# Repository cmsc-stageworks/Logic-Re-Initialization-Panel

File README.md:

# Logic Initialization Panel

Created by the BYU IEEE Branch for the CMSC

## Overview
The idea is that you take an isolinear chip that is "broken" and you place it in to have a certain logic circuit "fixed/repaired" the screen gives you a guide to be able to solve the puzzle/prompt. you then "write" it to the card

### Puzzle setup
The puzzle would consist of a series of (up to) 4 inputs and (up to) 4 outputs. These inputs could be things such as "Engine overheating" or "Autorization level 4 is given" or "Fire detected". The outputs could be "Turn on cooling fans" or "Override safety protocols" or "open airlock" etc. The user would be responsible for implemmenting the logic necessary to solve the puzzle at hand. 

### Interactivity
The user can test inputs manually by pressing the 4 buttons off to the input side of the logic panel, turning them on or off (true or false). They can then visually see how the logic would travel step by step in their current circuit.

### Completion
When they are ready to submit they hit the write button and it tests their circuit to verify correctness. If it is incorrect it throws an error and lets them try again. If it is correct it "writes" it to the card and they can move the card back to its original position to "fix" or "optimize" a system

## Learning outcomes
This panel teaches basic boolean logic (not, and, or) to children, or can be configured to challenge adults with more gates/configurations.

### Gate holder

### Initial Concept
Will be cut down, since this was originally started as a whole panel idea and was cut down to be a sub-panel.

### Magnet Codes:
[logic_puzzle_addresses.txt](logic_puzzle_addresses.txt)
### File system
[Proposed File System](FileSystem.md)

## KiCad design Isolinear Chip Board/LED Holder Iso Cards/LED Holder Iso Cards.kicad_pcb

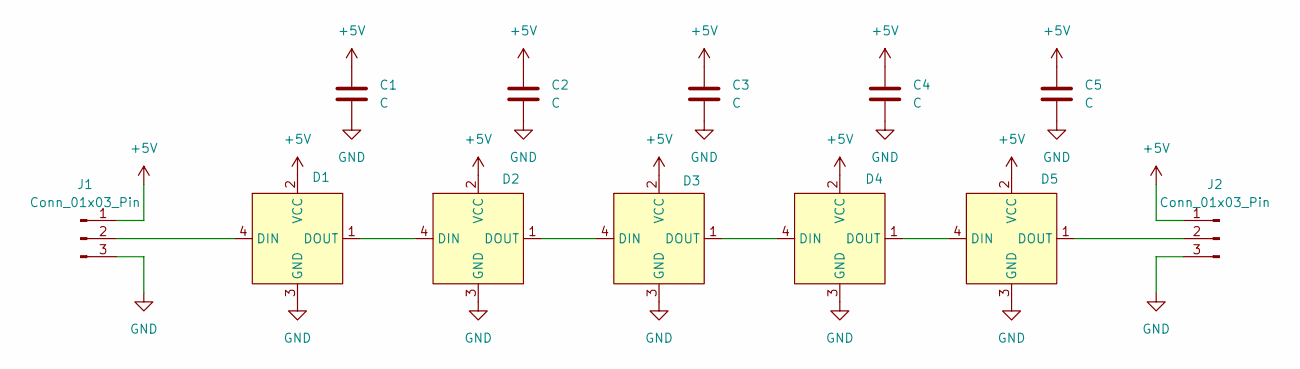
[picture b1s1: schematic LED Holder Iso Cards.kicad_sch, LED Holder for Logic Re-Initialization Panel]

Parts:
C1, C2, C3, C4, C5: C; C_Disc_D3.0mm_W1.6mm_P2.50mm
D1, D2, D3, D4, D5: NeoPixel_THT; LED_D5.0mm-4_RGB_Staggered_Pins
J1, J2: Conn_01x03_Pin; JST_XH_B3B-XH-AM_1x03_P2.50mm_Vertical

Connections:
+5V: C1.1, C2.1, C3.1, C4.1, C5.1, D1.2 (VCC), D2.2 (VCC), D3.2 (VCC), D4.2 (VCC), D5.2 (VCC), J1.1, J2.1
GND: C1.2, C2.2, C3.2, C4.2, C5.2, D1.3 (GND), D2.3 (GND), D3.3 (GND), D4.3 (GND), D5.3 (GND), J1.3, J2.3
unnamed: D1.4 (DIN), J1.2
unnamed: D1.1 (DOUT), D2.4 (DIN)
unnamed: D2.1 (DOUT), D3.4 (DIN)
unnamed: D3.1 (DOUT), D4.4 (DIN)
unnamed: D4.1 (DOUT), D5.4 (DIN)
unnamed: D5.1 (DOUT), J2.2

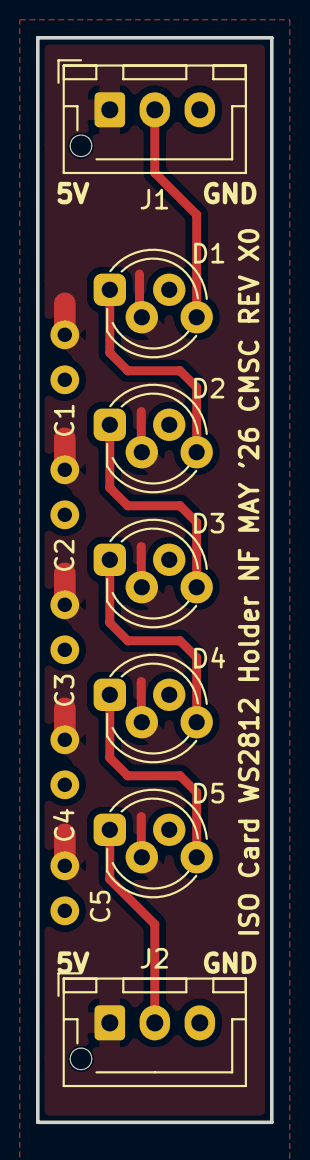
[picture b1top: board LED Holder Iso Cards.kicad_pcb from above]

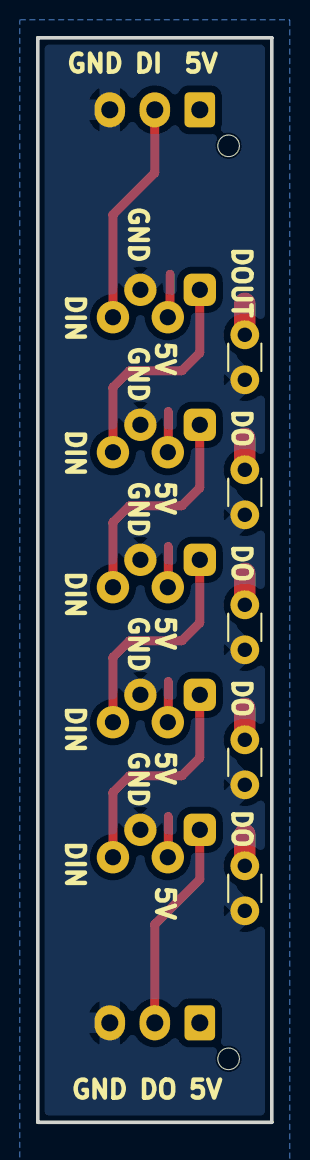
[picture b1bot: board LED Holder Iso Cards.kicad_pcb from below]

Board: 2 copper layers, 13.0 x 60.2 mm, 12 parts (5 on the bottom side), 8 nets.

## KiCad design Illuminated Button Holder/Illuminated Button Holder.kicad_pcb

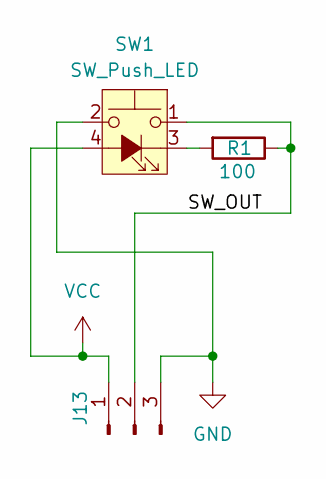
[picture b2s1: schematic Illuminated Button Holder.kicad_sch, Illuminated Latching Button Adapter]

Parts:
J13: Conn_01x03_Pin; JST_PH_B3B-PH-K_1x03_P2.00mm_Vertical
R1: 100; R_0805_2012Metric_Pad1.20x1.40mm_HandSolder
SW1: SW_Push_LED; Pushbutton

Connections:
/SW_OUT: J13.2, R1.1, SW1.1
GND: J13.3, SW1.2
unnamed: R1.2, SW1.3 (K)
VCC: J13.1, SW1.4 (A)

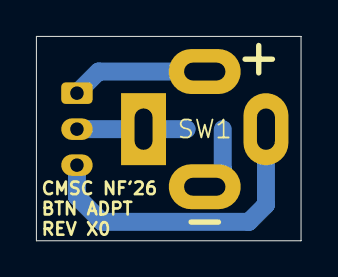
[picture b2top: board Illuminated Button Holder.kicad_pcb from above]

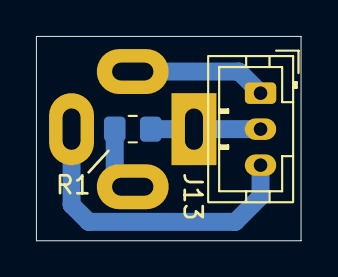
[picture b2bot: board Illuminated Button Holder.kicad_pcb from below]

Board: 2 copper layers, 14.7 x 11.4 mm, 3 parts (2 on the bottom side), 4 nets.

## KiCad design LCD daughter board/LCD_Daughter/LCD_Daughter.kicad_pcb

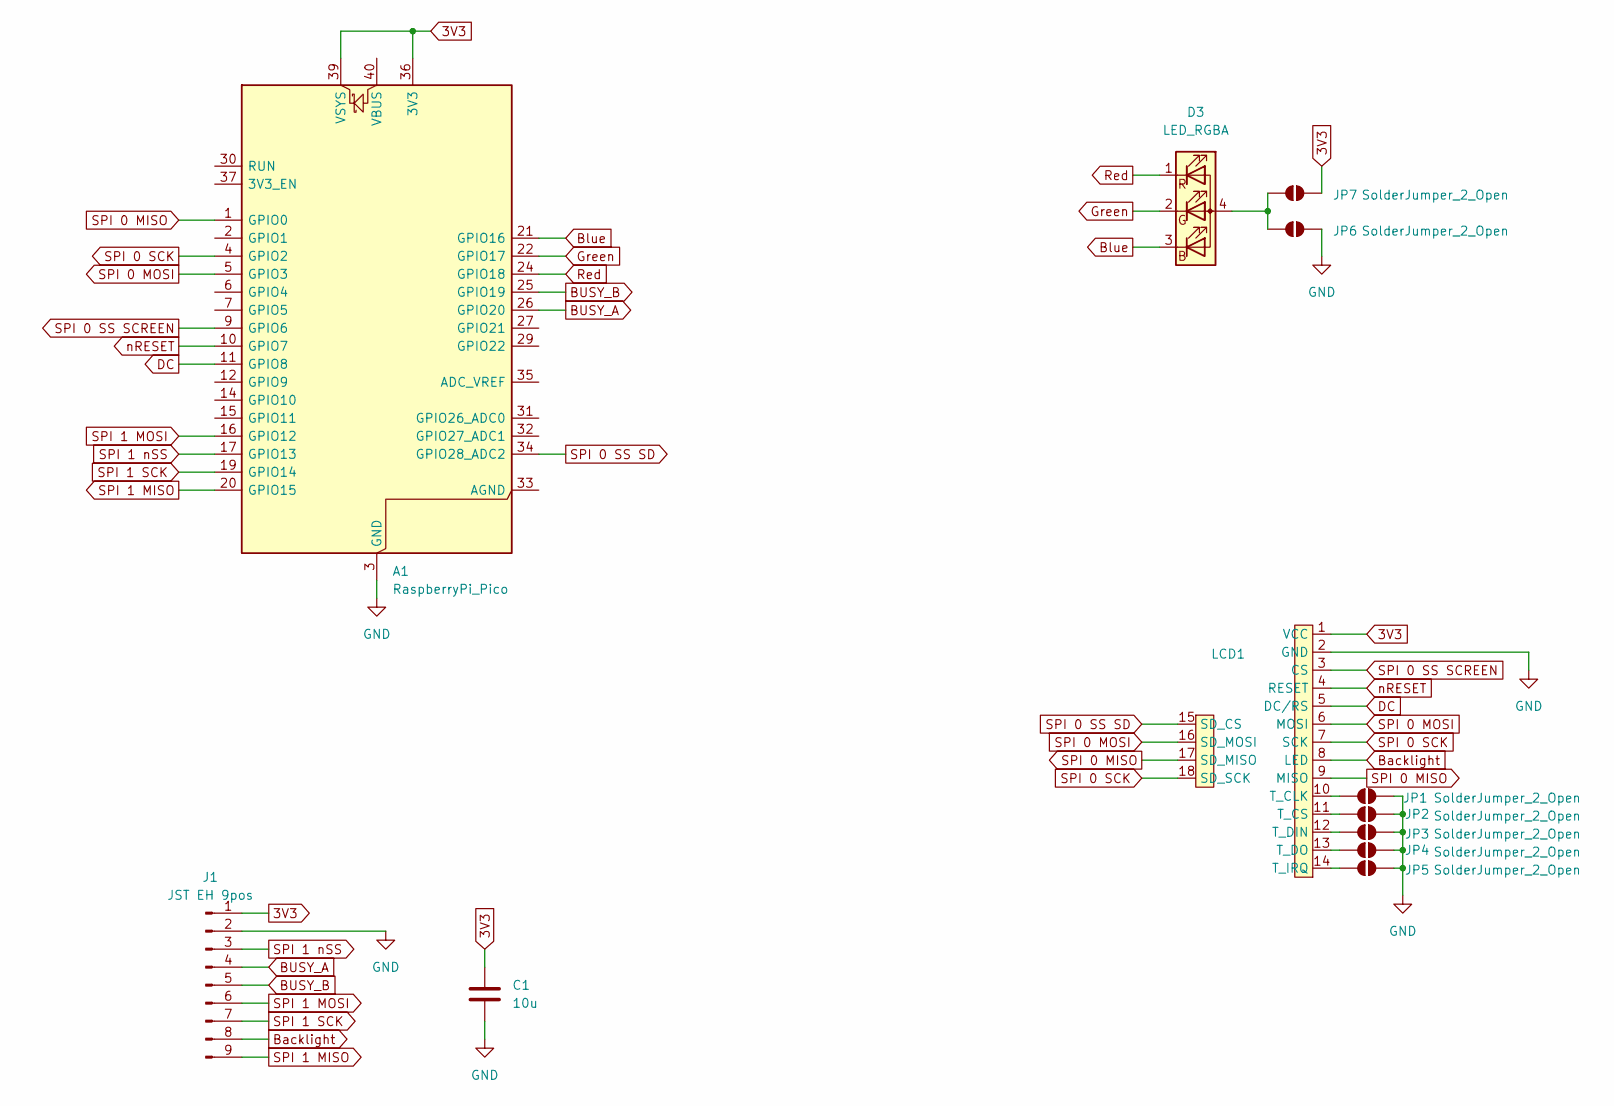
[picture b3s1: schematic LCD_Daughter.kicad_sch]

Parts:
A1: RaspberryPi_Pico; RaspberryPi_Pico_Common_Unspecified
C1: 10u; C_Disc_D3.0mm_W2.0mm_P2.50mm
D3: LED_RGBA; LED_D5.0mm-4_RGB_Staggered_Pins
J1: JST EH 9pos; JST_EH_B9B-EH-A_1x09_P2.50mm_Vertical
JP1, JP2, JP3, JP4, JP5, JP6, JP7: SolderJumper_2_Open; SolderJumper-2_P1.3mm_Open_TrianglePad1.0x1.5mm
LCD1: LCD

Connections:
3V3: A1.36 (3V3), A1.39 (VSYS), C1.1, J1.1, JP7.2 (B), LCD1.1 (VCC)
BUSY_A: A1.26 (GPIO20), J1.4
BUSY_B: A1.25 (GPIO19), J1.5
Backlight: J1.8, LCD1.8 (LED)
Blue: A1.21 (GPIO16), D3.3 (BK)
DC: A1.11 (GPIO8), LCD1.5 (DC/RS)
GND: A1.3 (GND), A1.8 (GND), A1.13 (GND), A1.18 (GND), A1.23 (GND), A1.28 (GND), A1.38 (GND), C1.2, J1.2, JP1.2 (B), JP2.2 (B), JP3.2 (B), JP4.2 (B), JP5.2 (B), JP6.2 (B), LCD1.2 (GND)
Green: A1.22 (GPIO17), D3.2 (GK)
unnamed: D3.4 (A), JP6.1 (A), JP7.1 (A)
unnamed: JP1.1 (A), LCD1.10 (T_CLK)
unnamed: JP2.1 (A), LCD1.11 (T_CS)
unnamed: JP3.1 (A), LCD1.12 (T_DIN)
unnamed: JP4.1 (A), LCD1.13 (T_DO)
unnamed: JP5.1 (A), LCD1.14 (T_IRQ)
Red: A1.24 (GPIO18), D3.1 (RK)
SPI 0 MISO: A1.1 (GPIO0), LCD1.9 (MISO), LCD1.17 (SD_MISO)
SPI 0 MOSI: A1.5 (GPIO3), LCD1.6 (MOSI), LCD1.16 (SD_MOSI)
SPI 0 SCK: A1.4 (GPIO2), LCD1.7 (SCK), LCD1.18 (SD_SCK)
SPI 0 SS SCREEN: A1.9 (GPIO6), LCD1.3 (CS)
SPI 0 SS SD: A1.34 (GPIO28_ADC2), LCD1.15 (SD_CS)
SPI 1 MISO: A1.20 (GPIO15), J1.9
SPI 1 MOSI: A1.16 (GPIO12), J1.6
SPI 1 SCK: A1.19 (GPIO14), J1.7
SPI 1 nSS: A1.17 (GPIO13), J1.3
nRESET: A1.10 (GPIO7), LCD1.4 (RESET)

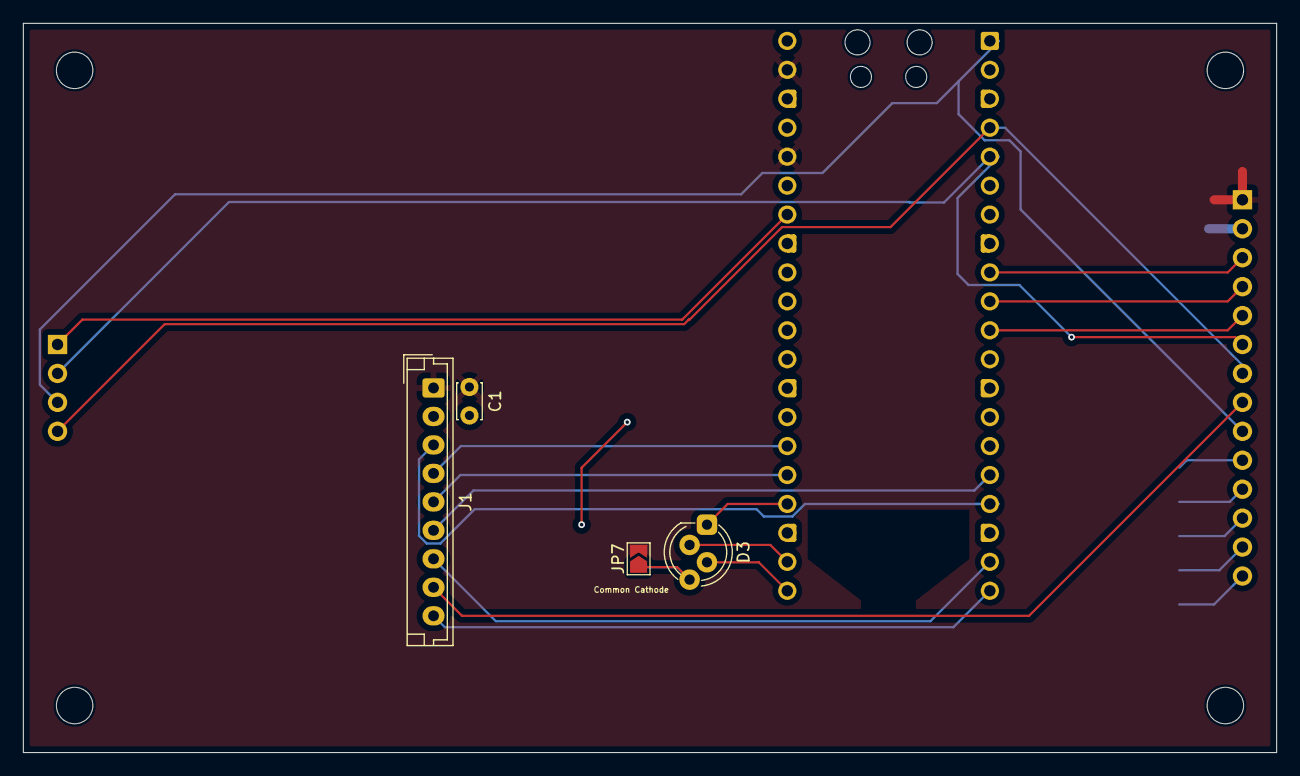
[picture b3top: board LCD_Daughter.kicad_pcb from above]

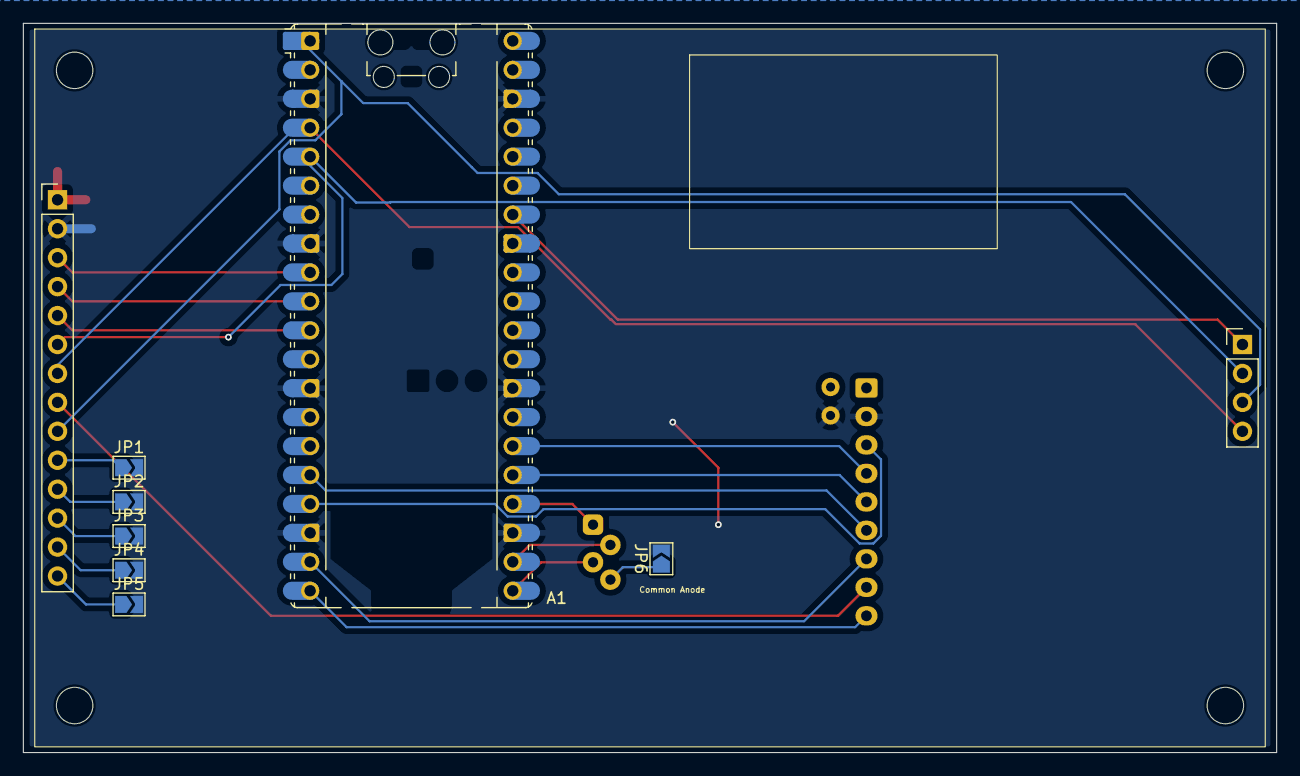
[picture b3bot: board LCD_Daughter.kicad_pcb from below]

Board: 2 copper layers, 110.0 x 64.0 mm, 12 parts (8 on the bottom side), 25 nets.

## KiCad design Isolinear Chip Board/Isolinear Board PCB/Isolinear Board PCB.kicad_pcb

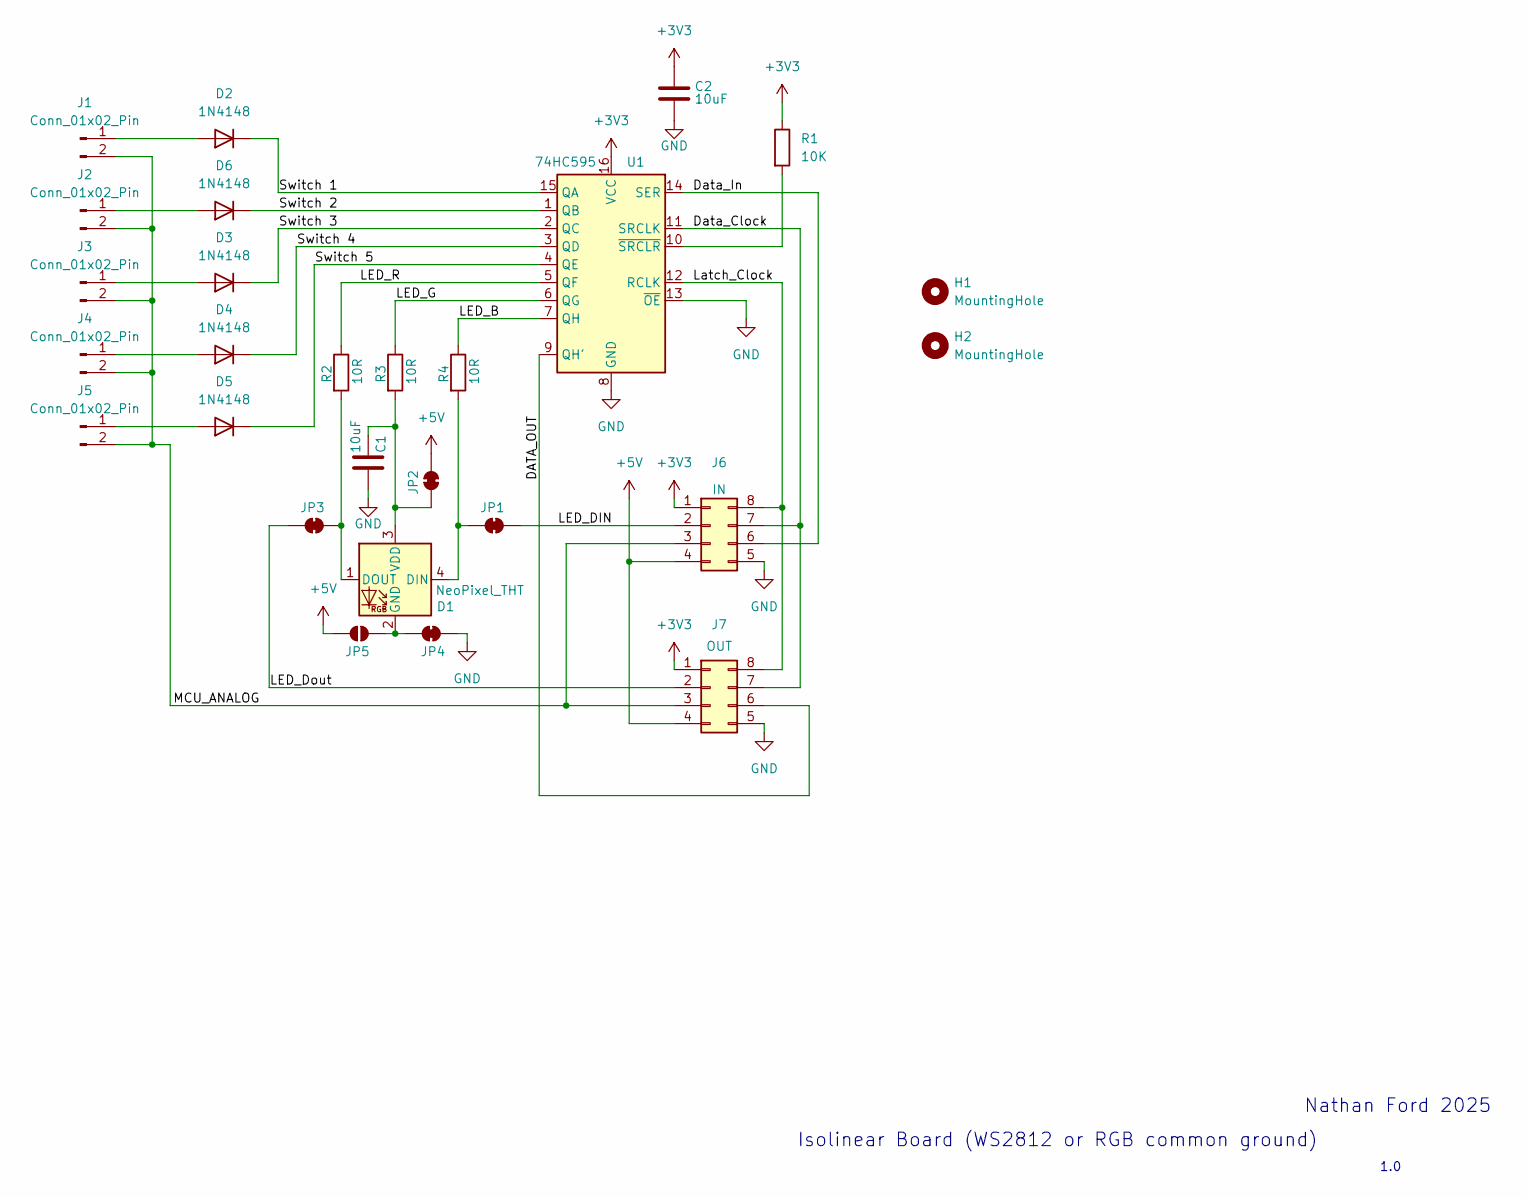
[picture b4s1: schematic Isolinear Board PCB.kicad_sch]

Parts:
C1, C2: 10uF; C_Disc_D5.0mm_W2.5mm_P5.00mm
D1: NeoPixel_THT; LED_D5.0mm-4_RGB_Staggered_Pins
D2, D3, D4, D5, D6: 1N4148; D_DO-35_SOD27_P7.62mm_Horizontal
H1: MountingHole; MountingHole_3.2mm_M3
H2: MountingHole; MountingHole_2.1mm
J1, J2, J3, J4, J5: Conn_01x02_Pin; JST_XH_B02B-XH-A_02x2.50mm_Straight
J6: IN; IDC-Header_2x04_P2.54mm_Vertical
J7: OUT; IDC-Header_2x04_P2.54mm_Vertical
JP1, JP2, JP3, JP4: SolderJumper_2_Bridged; SolderJumper-2_P1.3mm_Bridged2Bar_RoundedPad1.0x1.5mm
JP5: SolderJumper_2_Open; SolderJumper-2_P1.3mm_Open_RoundedPad1.0x1.5mm
R1: 10K; R_Axial_DIN0207_L6.3mm_D2.5mm_P7.62mm_Horizontal
R2, R3, R4: 10R; R_Axial_DIN0207_L6.3mm_D2.5mm_P7.62mm_Horizontal
U1: 74HC595; DIP-16_W7.62mm_LongPads

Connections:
+3V3: C2.1, J6.1, J7.1, R1.1, U1.16 (VCC)
+5V: J6.4, J7.4, JP2.2 (B), JP5.1 (A)
/DATA_OUT: J7.6, U1.9 (QH')
/Data_Clock: J6.7, J7.7, U1.11 (SRCLK)
/Data_In: J6.6, U1.14 (SER)
/LED_B: R4.1, U1.7 (QH)
/LED_DIN: J6.2, JP1.2 (B)
/LED_Dout: J7.2, JP3.1 (A)
/LED_G: R3.1, U1.6 (QG)
/LED_R: R2.1, U1.5 (QF)
/Latch_Clock: J6.8, J7.8, U1.12 (RCLK)
/MCU_ANALOG: J1.2, J2.2, J3.2, J4.2, J5.2, J6.3, J7.3
/Switch 1: D2.1 (K), U1.15 (QA)
/Switch 2: D6.1 (K), U1.1 (QB)
/Switch 3: D3.1 (K), U1.2 (QC)
/Switch 4: D4.1 (K), U1.3 (QD)
/Switch 5: D5.1 (K), U1.4 (QE)
GND: C1.2, C2.2, J6.5, J7.5, JP4.2 (B), U1.8 (GND), U1.13 (~OE)
unnamed: D1.4 (DIN), JP1.1 (A), R4.2
unnamed: D1.1 (DOUT), JP3.2 (B), R2.2
unnamed: D1.2 (GND), JP4.1 (A), JP5.2 (B)
unnamed: C1.1, D1.3 (VDD), JP2.1 (A), R3.2
unnamed: D2.2 (A), J1.1
unnamed: D3.2 (A), J3.1
unnamed: D4.2 (A), J4.1
unnamed: D5.2 (A), J5.1
unnamed: D6.2 (A), J2.1
unnamed: R1.2, U1.10 (~SRCLR)

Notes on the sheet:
Isolinear Board (WS2812 or RGB common ground)
1.0
Nathan Ford 2025

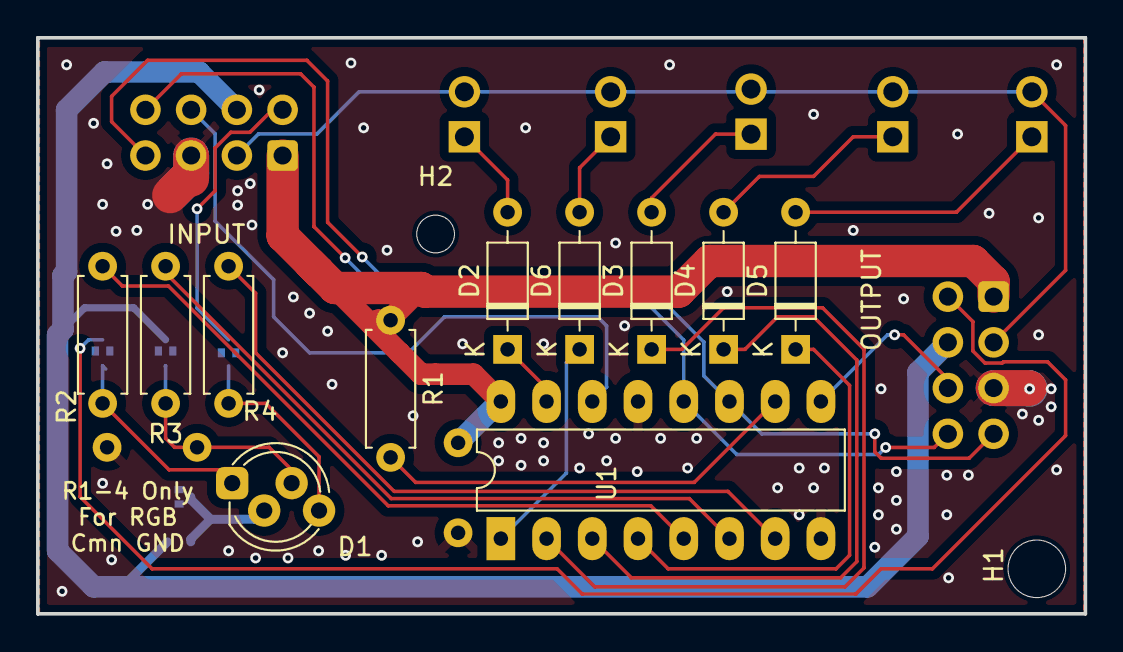
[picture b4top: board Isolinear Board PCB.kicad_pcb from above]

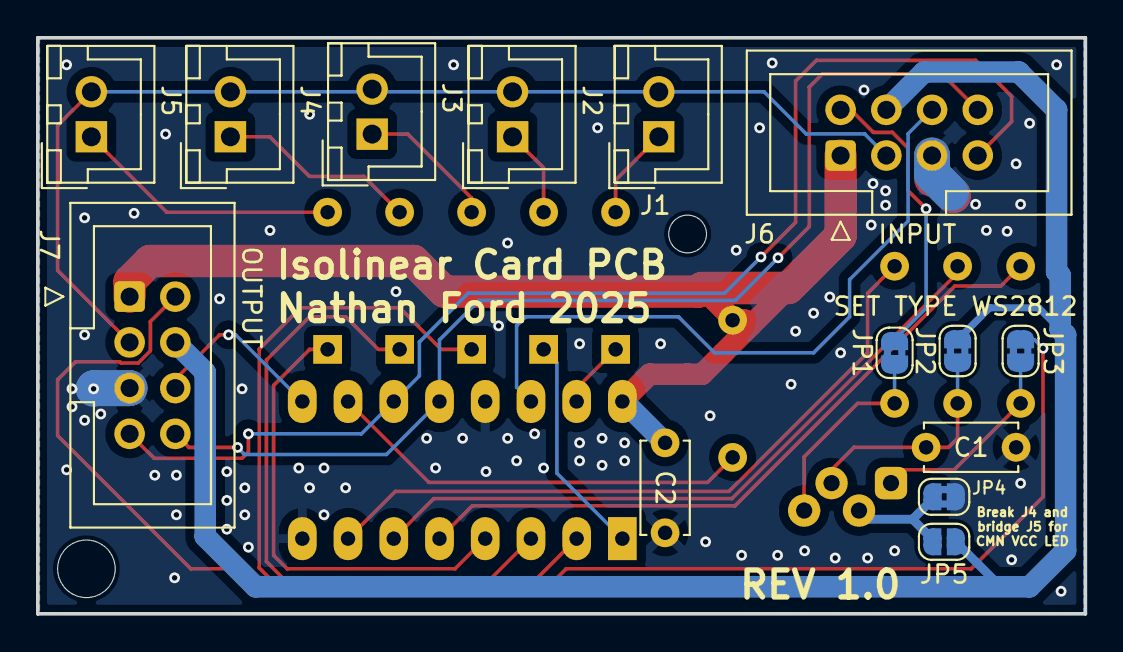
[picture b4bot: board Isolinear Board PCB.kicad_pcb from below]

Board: 2 copper layers, 58.2 x 32.0 mm, 27 parts (14 on the bottom side), 28 nets.

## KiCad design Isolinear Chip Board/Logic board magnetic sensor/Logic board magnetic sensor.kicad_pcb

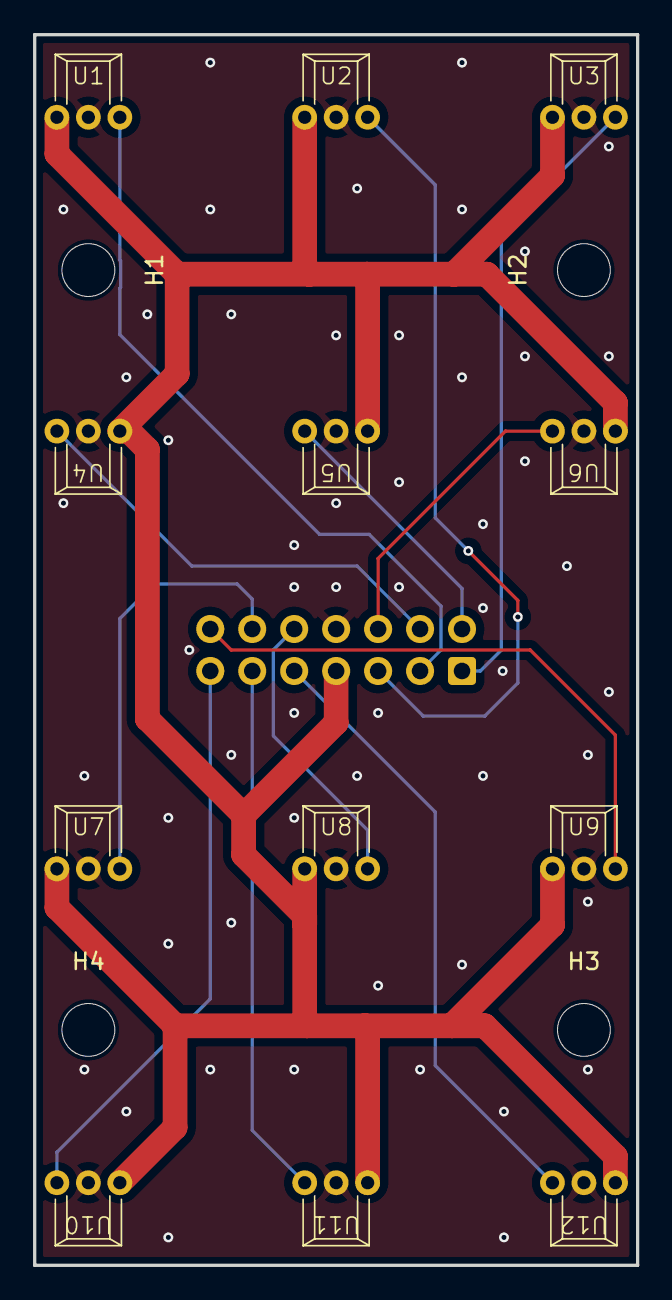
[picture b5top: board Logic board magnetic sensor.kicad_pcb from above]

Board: 2 copper layers, 36.5 x 74.5 mm, 17 parts (1 on the bottom side), 14 nets.

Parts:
H1, H2, H3, H4: MountingHole; MountingHole_3.2mm_M3
J2: Conn_02x07_Odd_Even; IDC-Header_2x07_P2.54mm_Vertical
U1, U2, U3, U4, U5, U6, U7, U8, U9, U10, U11, U12: Linear Hall Effect Sensor SS49E

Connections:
GND: J2.8, U1.2 (GND), U2.2 (GND), U3.2 (GND), U4.2 (GND), U5.2 (GND), U6.2 (GND), U7.2 (GND), U8.2 (GND), U9.2 (GND), U10.2 (GND), U11.2 (GND), U12.2 (GND)
unnamed: J2.1, U3.3 (OUT)
unnamed: J2.2, U5.3 (OUT)
unnamed: J2.3, U1.3 (OUT)
unnamed: J2.4, U4.3 (OUT)
unnamed: J2.5, U2.3 (OUT)
unnamed: J2.6, U6.3 (OUT)
unnamed: J2.9, U12.3 (OUT)
unnamed: J2.10, U8.3 (OUT)
unnamed: J2.11, U11.3 (OUT)
unnamed: J2.12, U7.3 (OUT)
unnamed: J2.13, U10.3 (OUT)
unnamed: J2.14, U9.3 (OUT)
VCC: J2.7, U1.1 (VDD), U2.1 (VDD), U3.1 (VDD), U4.1 (VDD), U5.1 (VDD), U6.1 (VDD), U7.1 (VDD), U8.1 (VDD), U9.1 (VDD), U10.1 (VDD), U11.1 (VDD), U12.1 (VDD)

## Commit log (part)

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2025-09-20 Initial Move-Over from susbystem documentation
    This was all moved over from the Subsystem Documentation repository, to its own new repository
2025-09-26 moved 3d models
2025-09-26 added concept drawing for future reference
2025-09-26 Move STL files and add project README
    Moved STL files to the '3D Models/Apollo Gauge' directory for better organization. Added a README.md describing the Logic Initialization Panel project, its purpose, and educational goals.
2025-09-26 Renamed File
2025-09-26 added codes and more text to readme
2025-10-08 Add STEP models for headers and display
    Added 3D STEP files for 14 pin female header, 4 pin female header, and ST7796S Display v7. Included a readme and terms of use for the 14 pin header model.
2025-10-10 Add images and update README with project details
    Added new images for gate renders and logic gate examples, and moved InitialConcept.jpg to the Images directory. Updated README.md to include an overview, puzzle setup, interactivity, completion step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
2025-10-17 Made the LCD daughter board
2025-10-19 Added code repo for the screens
2025-10-19 Fixed bug
2025-10-23 updated code
2025-10-24 Renamed SPI busses to match RPI's names. Fixed code to use the correct SPI busses.
2025-12-24 Started work on logic panel code
2025-12-24 First working prototype
    Only reads the first 4 ports but otherwise works
2025-12-24 Improve gate status serial output formatting
    Updated the loop to print gate statuses in a 4x4 grid format, providing clearer visualization of current gate states for debugging.
2025-12-28 Created PCB for the LEDs on the Logic Panel
2025-12-28 Add Isolinear Chips NFC 3D model files
    Added new 3D model files for the Isolinear Chips NFC project, including Card Holder, Clip, Iso Card Body, Iso Card Diffuser, and a print profile. These files support the creation and printing of NFC-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
2025-12-29 added logic board source file
2025-12-30 Updated code to fit in with other code
2025-12-30 Rename logic_board files to logic_evaluator
    Renamed logic_board.cpp and logic_board.h to logic_evaluator.cpp and logic_evaluator.h, respectively, to better reflect their purpose.
2025-12-31 Add ISO card NFC support and unit tests
    Introduced isoCards library for handling ISO card NFC readers, including initialization, card management, and serialization. Updated platformio.ini to include Adafruit PN532 dependency. Added unit te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
2026-01-01 St7796S code, however CS is not asserting for some reason, Am going to try other library after this
    Integrated Adafruit_ST7796S library for dual LCD support, initialized two ST7796S displays, and added related pin definitions. Reduced SPI frequency from 80MHz to 30MHz for compatibility. Updated dep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
2026-01-02 added debug to the screen
2026-01-03 Logic Cards now work, added proposed File System
2026-01-03 Updated Main Readme
2026-01-09 Kicad LCD daughterboard
2026-01-09 Started work on logic wire lights (unfinished commit)
2026-05-31 NFC tag reader operational and Button holder PCB files
    Got ISO cards reading and writing
    Uploaded PCB for ISO card reader LEDs
2026-05-31 updated timout len to be tighter
2026-05-31 Prompt is now written to screen with ISO card
    - Iso cards now link to their puzzles and show the appropriate image
2026-06-01 now can check for solutions
